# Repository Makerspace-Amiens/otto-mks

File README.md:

# Otto-MKS
Open Source Robot based on Otto, the Walking Robot

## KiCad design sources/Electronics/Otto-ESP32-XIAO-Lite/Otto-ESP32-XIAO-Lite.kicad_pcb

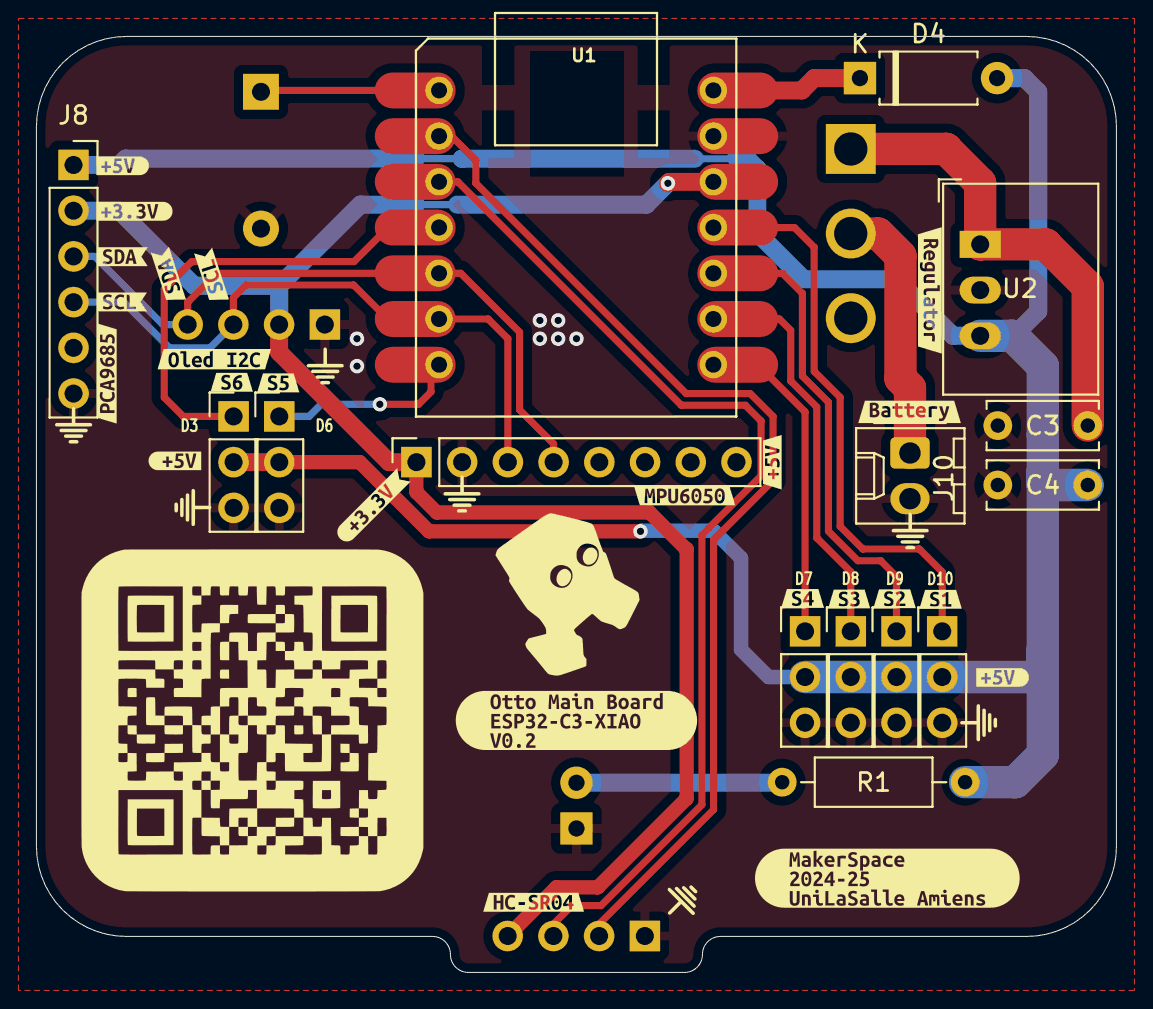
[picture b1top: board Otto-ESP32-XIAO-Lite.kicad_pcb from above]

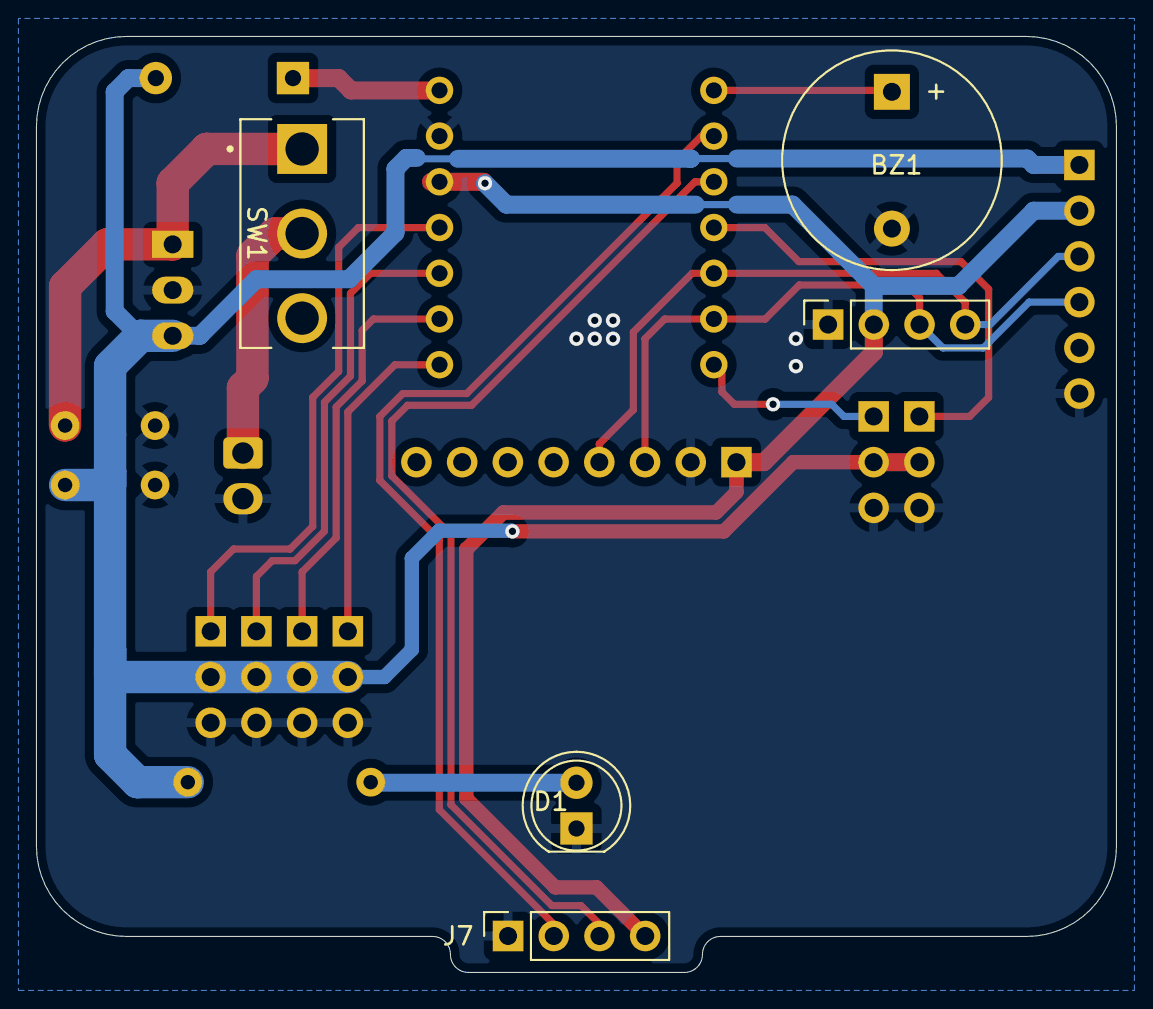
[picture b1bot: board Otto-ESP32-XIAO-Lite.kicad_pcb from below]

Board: 2 copper layers, 60.0 x 52.0 mm, 44 parts (5 on the bottom side), 18 nets.

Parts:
BZ1: Buzzer; Buzzer_12x9.5RM7.6
C3, C4: C_Small; C_Disc_D6.0mm_W2.5mm_P5.00mm
D1: LED_Small; LED_D5.0mm
D4: D_Schottky; D_A-405_P7.62mm_Horizontal
J1, J2, J3, J4, J5, J6: Conn_01x03; PinHeader_1x03_P2.54mm_Vertical
J7: Ultrasonic sensor; PinSocket_1x04_P2.54mm_Vertical
J8: PCA9685; PinSocket_1x06_P2.54mm_Vertical
J10: Conn_01x02; Molex_KK-254_AE-6410-02A_1x02_P2.54mm_Vertical
J12: OLED 0,91" - I2C (SKU21796); PinSocket_1x04_P2.54mm_Vertical
J13: MPU6050; PinSocket_1x08_P2.54mm_Vertical
R1: R_Small; R_Axial_DIN0207_L6.3mm_D2.5mm_P10.16mm_Horizontal
SW1: SW_SPDT; SW_100SP1T1B4M2QE
U1: MOUDLE-SEEEDUINO-XIAO-ESP32C3; MOUDLE14P-SMD-2.54-21X17.8MM
U2: R-78E5.0-1.0; Converter_DCDC_RECOM_R-78E-0.5_THT
kibuzzard-66E45AAF: G***; kibuzzard-66E45AAF
kibuzzard-66E45B4D: G***; kibuzzard-66E45B4D
kibuzzard-66E45B8A: G***; kibuzzard-66E45B8A
kibuzzard-66E45B15: G***; kibuzzard-66E45B15
kibuzzard-66E45B47: G***; kibuzzard-66E45B47
kibuzzard-66E45B51: G***; kibuzzard-66E45B51
kibuzzard-66E45B85: G***; kibuzzard-66E45B85
kibuzzard-66E45BAB, kibuzzard-66E45BAB#2: G***; kibuzzard-66E45BAB
kibuzzard-66E45BBF: G***; kibuzzard-66E45BBF
kibuzzard-66E45BE1: G***; kibuzzard-66E45BE1
kibuzzard-66E45BF0: G***; kibuzzard-66E45BF0
kibuzzard-66E460A4: G***; kibuzzard-66E460A4
kibuzzard-66E460BA: G***; kibuzzard-66E460BA
kibuzzard-66E460D9: G***; kibuzzard-66E460D9
kibuzzard-66E46157: G***; kibuzzard-66E46157
kibuzzard-6707C6B3: G***; kibuzzard-6707C6B3
kibuzzard-6707CFA2: G***; kibuzzard-6707CFA2
kibuzzard-69711E0F: G***; kibuzzard-69711E0F
kibuzzard-676543B8: G***; kibuzzard-676543B8
kibuzzard-6765451E: G***; kibuzzard-6765451E
kibuzzard-6765454D: G***; kibuzzard-6765454D
kibuzzard-67654523: G***; kibuzzard-67654523
kibuzzard-67654588: G***; kibuzzard-67654588

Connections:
+3.3V: J7.4, J8.2, J12.2, J13.1, U1.12 (3V3)
+5V: C4.1, D4.2 (A), J1.2, J2.2, J3.2, J4.2, J5.2, J6.2, J8.1, R1.1, U2.3 (OUT)
+BATT: C3.1, SW1.1 (A), U2.1 (IN)
Buzzer: BZ1.1 (+), U1.1 (PA02_A0_D0)
Echo: J7.2, U1.2 (PA4_A1_D1)
GND: BZ1.2 (-), C3.2, C4.2, D1.1 (K), J1.3, J2.3, J3.3, J4.3, J5.3, J6.3, J7.1, J8.6, J10.2, J12.1, J13.2, U1.13 (GND), U2.2 (GND)
unnamed: D1.2 (A), R1.2
unnamed: D4.1 (K), U1.14 (5V)
unnamed: J10.1, SW1.2 (B)
SCL: J8.4, J12.3, J13.3, U1.6 (PA9_A5_D5_SCL)
SDA: J8.3, J12.4, J13.4, U1.5 (PA8_A4_D4_SDA)
Servo-1: J1.1, U1.11 (PA6_A10_D10_MOSI)
Servo-2: J2.1, U1.10 (PA5_A9_D9_MISO)
Servo-3: J3.1, U1.9 (PA7_A8_D8_SCK)
Servo-4: J4.1, U1.8 (PB09_A7_D7_RX)
Servo-5: J5.1, U1.7 (PB08_A6_D6_TX)
Servo-6: J6.1, U1.4 (PA11_A3_D3)
Trig: J7.3, U1.3 (PA10_A2_D2)

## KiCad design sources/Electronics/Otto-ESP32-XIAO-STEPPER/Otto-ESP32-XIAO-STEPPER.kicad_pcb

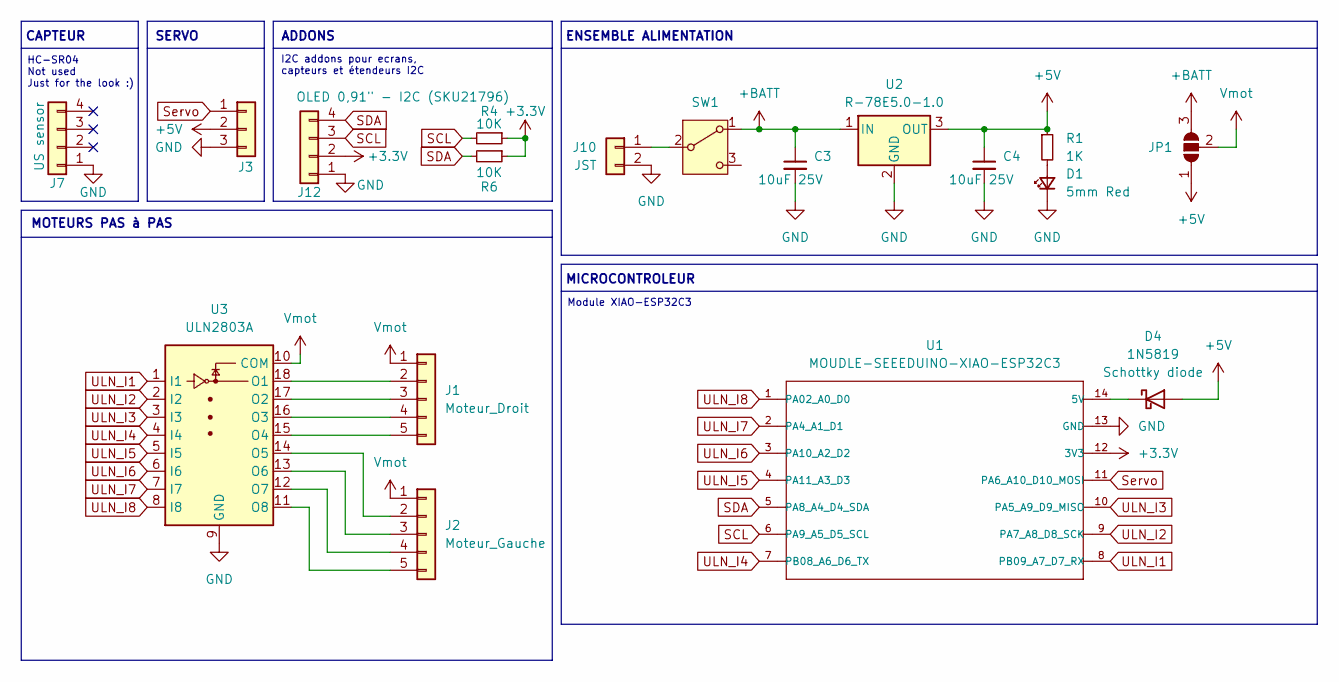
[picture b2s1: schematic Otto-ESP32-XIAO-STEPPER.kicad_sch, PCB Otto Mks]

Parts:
C3, C4: 10uF 25V; C_Disc_D6.0mm_W2.5mm_P5.00mm
D1: 5mm Red; LED_D5.0mm
D4: 1N5819; D_A-405_P7.62mm_Horizontal
J1: Moteur_Droit; JST_XH_B5B-XH-A_1x05_P2.50mm_Vertical
J2: Moteur_Gauche; JST_XH_B5B-XH-A_1x05_P2.50mm_Vertical
J3: Servo; PinHeader_1x03_P2.54mm_Vertical
J7: US sensor; PinSocket_1x04_P2.54mm_Vertical
J10: JST; Molex_KK-254_AE-6410-02A_1x02_P2.54mm_Vertical
J12: OLED 0,91" - I2C (SKU21796); PinSocket_1x04_P2.54mm_Vertical
JP1: SolderJumper_3_Open; SolderJumper-3_P2.0mm_Open_TrianglePad1.0x1.5mm
R1: 1K; R_Axial_DIN0207_L6.3mm_D2.5mm_P10.16mm_Horizontal
R4, R6: 10K; R_1206_3216Metric_Pad1.30x1.75mm_HandSolder
SW1: SW_SPDT; SW_100SP1T1B4M2QE
U1: MOUDLE-SEEEDUINO-XIAO-ESP32C3; XIAO-ESP32C3-DIP
U2: R-78E5.0-1.0; Converter_DCDC_RECOM_R-78E-0.5_THT
U3: ULN2803A; DIP-18_W7.62mm_Socket_LongPads

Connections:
+3.3V: J12.2, R4.1, R6.1, U1.12 (3V3)
+5V: C4.1, D4.2 (A), J3.2, JP1.1 (A), R1.1, U2.3 (OUT)
+BATT: C3.1, JP1.3 (B), SW1.1 (A), U2.1 (IN)
GND: C3.2, C4.2, D1.1 (K), J3.3, J7.1, J10.2, J12.1, U1.13 (GND), U2.2 (GND), U3.9 (GND)
unnamed: D1.2 (A), R1.2
unnamed: D4.1 (K), U1.14 (5V)
unnamed: J1.2, U3.18 (O1)
unnamed: J1.3, U3.17 (O2)
unnamed: J1.4, U3.16 (O3)
unnamed: J1.5, U3.15 (O4)
unnamed: J2.2, U3.14 (O5)
unnamed: J2.3, U3.13 (O6)
unnamed: J2.4, U3.12 (O7)
unnamed: J2.5, U3.11 (O8)
unnamed: J10.1, SW1.2 (B)
SCL: J12.3, R4.2, U1.6 (PA9_A5_D5_SCL)
SDA: J12.4, R6.2, U1.5 (PA8_A4_D4_SDA)
Servo: J3.1, U1.11 (PA6_A10_D10_MOSI)
ULN_I1: U1.8 (PB09_A7_D7_RX), U3.1 (I1)
ULN_I2: U1.9 (PA7_A8_D8_SCK), U3.2 (I2)
ULN_I3: U1.10 (PA5_A9_D9_MISO), U3.3 (I3)
ULN_I4: U1.7 (PB08_A6_D6_TX), U3.4 (I4)
ULN_I5: U1.4 (PA11_A3_D3), U3.5 (I5)
ULN_I6: U1.3 (PA10_A2_D2), U3.6 (I6)
ULN_I7: U1.2 (PA4_A1_D1), U3.7 (I7)
ULN_I8: U1.1 (PA02_A0_D0), U3.8 (I8)
Vmot: J1.1, J2.1, JP1.2 (C), U3.10 (COM)

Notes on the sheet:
HC-SR04 Not used Just for the look :)
CAPTEUR
MOTEURS PAS à PAS
ADDONS
ENSEMBLE ALIMENTATION
SERVO
Module XIAO-ESP32C3
I2C addons pour ecrans, capteurs et étendeurs I2C
MICROCONTROLEUR

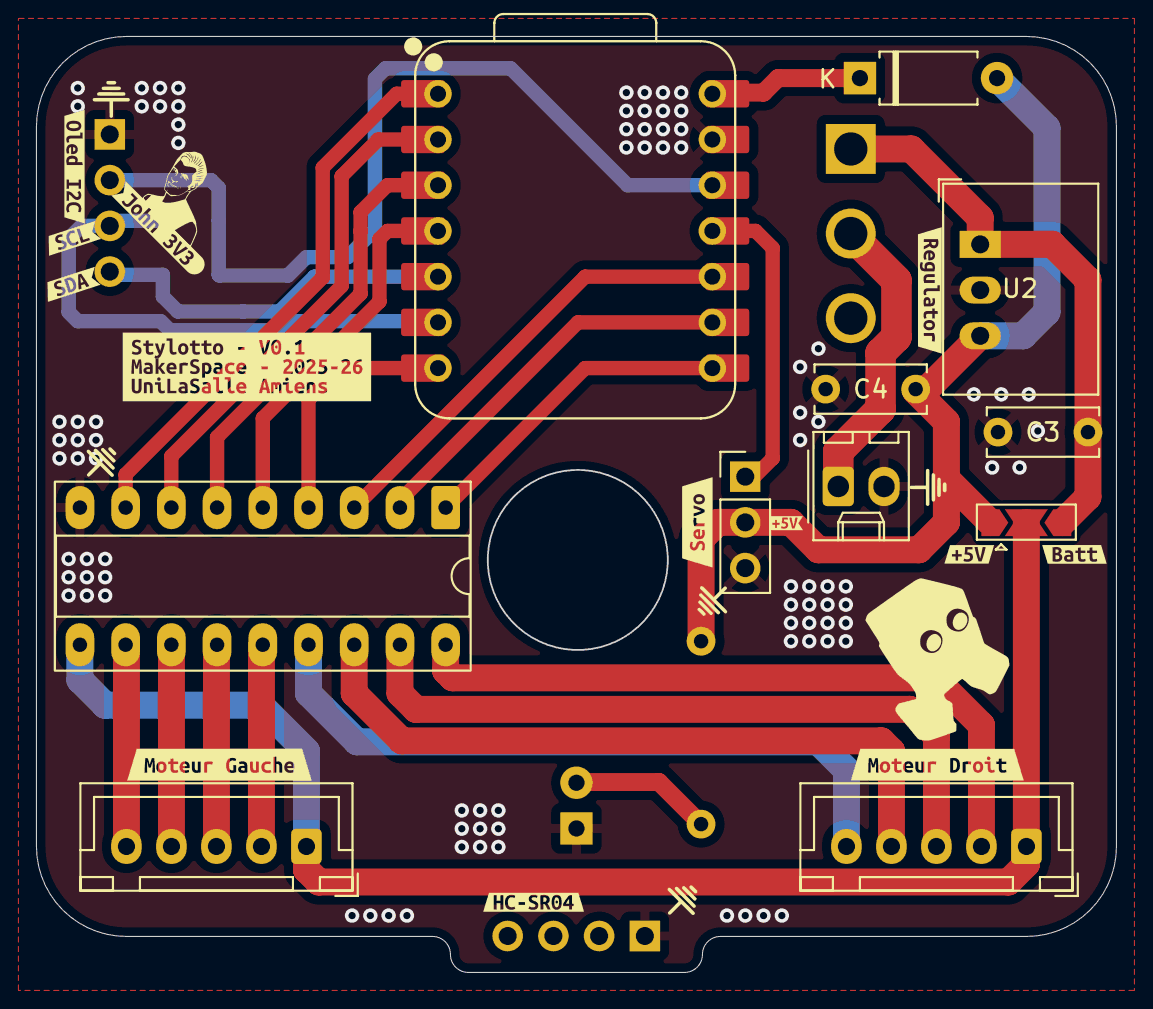
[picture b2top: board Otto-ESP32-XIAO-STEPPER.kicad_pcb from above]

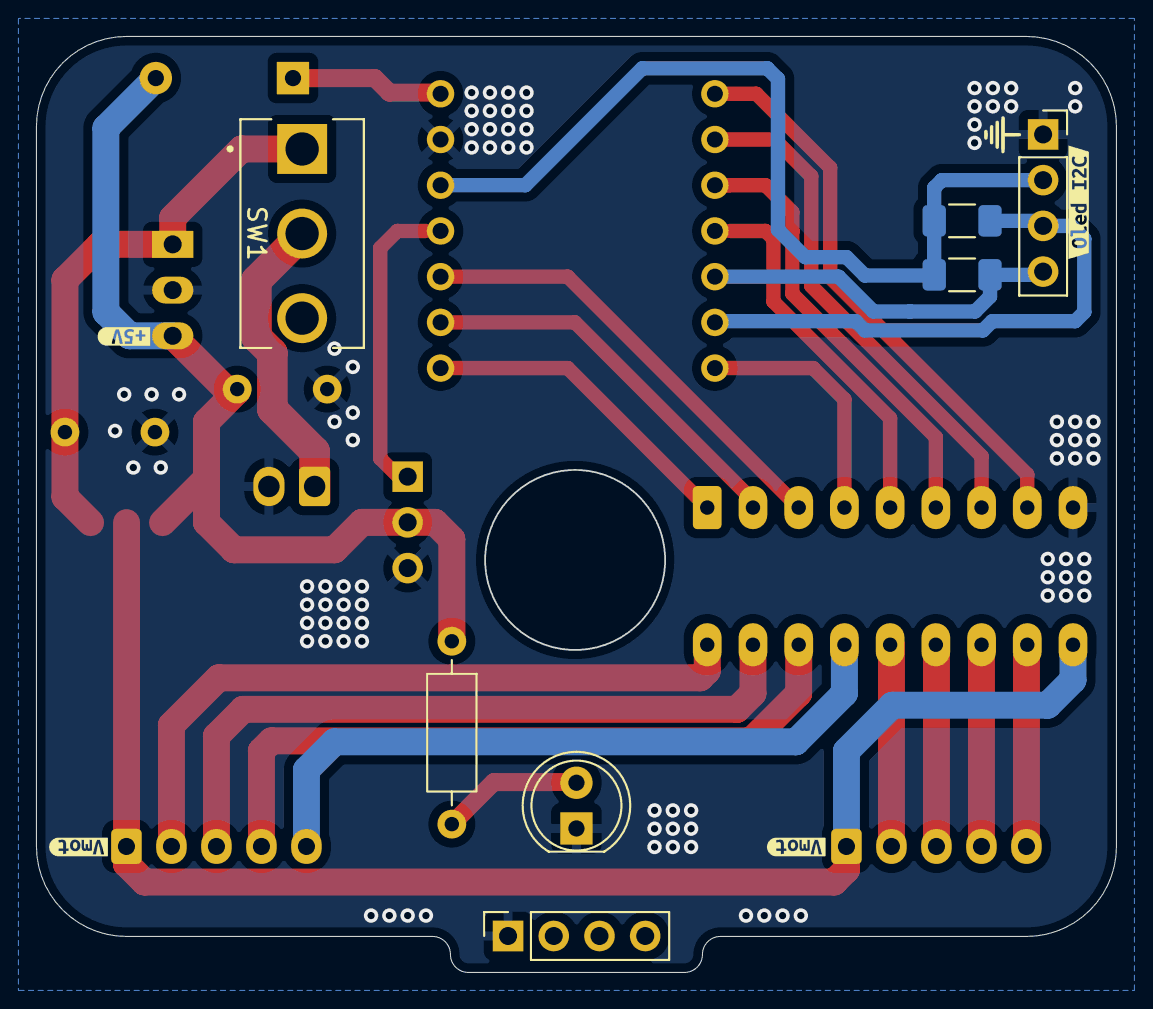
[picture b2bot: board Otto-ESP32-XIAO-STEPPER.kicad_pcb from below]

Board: 2 copper layers, 60.0 x 52.0 mm, 35 parts (11 on the bottom side), 27 nets.

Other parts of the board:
kibuzzard-66E45BAB: G***; kibuzzard-66E45BAB
kibuzzard-66E46157: G***; kibuzzard-66E46157
kibuzzard-67E17B13: G***; kibuzzard-67E17B13
kibuzzard-67E17CB8, kibuzzard-67E17CB8#2: G***; kibuzzard-67E17CB8
kibuzzard-68A443B3: G***; kibuzzard-68A443B3
kibuzzard-68A443C3: G***; kibuzzard-68A443C3
kibuzzard-68A443E1, kibuzzard-68A443E1#2: G***; kibuzzard-68A443E1
kibuzzard-68A4434B: G***; kibuzzard-68A4434B
kibuzzard-68A4489E: G***; kibuzzard-68A4489E
kibuzzard-68A44298: G***; kibuzzard-68A44298
kibuzzard-68A44346: G***; kibuzzard-68A44346
kibuzzard-68A44445: G***; kibuzzard-68A44445
kibuzzard-6707C6B3: G***; kibuzzard-6707C6B3
kibuzzard-6765451E: G***; kibuzzard-6765451E
kibuzzard-67654523: G***; kibuzzard-67654523

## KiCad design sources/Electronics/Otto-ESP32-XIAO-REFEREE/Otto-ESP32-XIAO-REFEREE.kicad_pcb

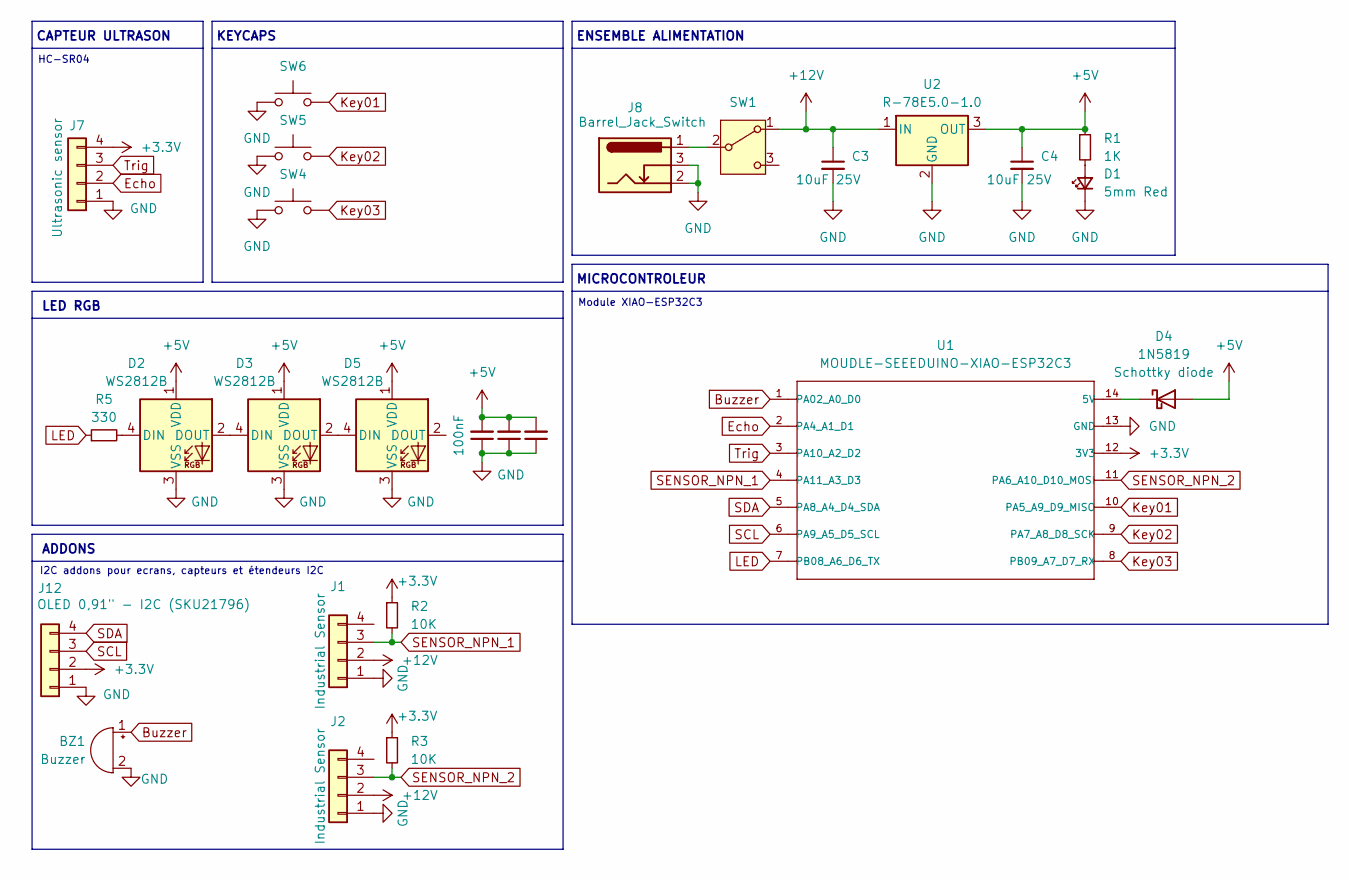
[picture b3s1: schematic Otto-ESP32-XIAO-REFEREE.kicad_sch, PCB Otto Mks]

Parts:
BZ1: Buzzer; Buzzer_12x9.5RM7.6
C3, C4: 10uF 25V; C_Disc_D6.0mm_W2.5mm_P5.00mm
C5, C6, C7: 100nF; C_1206_3216Metric_Pad1.33x1.80mm_HandSolder
D1: 5mm Red; LED_1206_3216Metric_Pad1.42x1.75mm_HandSolder
D2, D3, D5: WS2812B; LED_WS2812B_PLCC4_5.0x5.0mm_P3.2mm
D4: 1N5819; D_A-405_P7.62mm_Horizontal
J1, J2: Industrial Sensor; Molex_KK-254_AE-6410-04A_1x04_P2.54mm_Vertical
J7: Ultrasonic sensor; PinSocket_1x04_P2.54mm_Vertical
J8: Barrel_Jack_Switch; BarrelJack_Horizontal
J12: OLED 0,91" - I2C (SKU21796); PinSocket_1x04_P2.54mm_Vertical
R1: 1K; R_1206_3216Metric_Pad1.30x1.75mm_HandSolder
R2, R3: 10K; R_1206_3216Metric_Pad1.30x1.75mm_HandSolder
R5: 330; R_1206_3216Metric_Pad1.30x1.75mm_HandSolder
SW1: SW_SPDT; SW_100SP1T1B4M2QE
SW4, SW5, SW6: CherryMX; SW_Cherry_MX_1.00u_PCB
U1: MOUDLE-SEEEDUINO-XIAO-ESP32C3; XIAO-ESP32C3-DIP
U2: R-78E5.0-1.0; Converter_DCDC_RECOM_R-78E-0.5_THT

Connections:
+3.3V: J7.4, J12.2, R2.1, R3.1, U1.12 (3V3); also elsewhere on the board
+5V: C4.1, C5.2, C6.2, C7.2, D2.1 (VDD), D3.1 (VDD), D4.2 (A), D5.1 (VDD), R1.1, U2.3 (OUT)
+12V: C3.1, J1.2, J2.2, SW1.1 (A), U2.1 (IN)
Buzzer: BZ1.1 (+), U1.1 (PA02_A0_D0)
Echo: J7.2, U1.2 (PA4_A1_D1)
GND: BZ1.2 (-), C3.2, C4.2, C5.1, C6.1, C7.1, D1.1 (K), D2.3 (VSS), D3.3 (VSS), D5.3 (VSS), J1.1, J2.1, J7.1, J8.2, J8.3, J12.1, SW4.1, SW5.1, SW6.1, U1.13 (GND), U2.2 (GND)
Key01: SW6.2, U1.10 (PA5_A9_D9_MISO)
Key02: SW5.2, U1.9 (PA7_A8_D8_SCK)
Key03: SW4.2, U1.8 (PB09_A7_D7_RX)
LED: R5.1, U1.7 (PB08_A6_D6_TX)
unnamed: D1.2 (A), R1.2
unnamed: D2.4 (DIN), R5.2
unnamed: D2.2 (DOUT), D3.4 (DIN)
unnamed: D3.2 (DOUT), D5.4 (DIN)
unnamed: D4.1 (K), U1.14 (5V)
unnamed: J8.1, SW1.2 (B)
SCL: J12.3, U1.6 (PA9_A5_D5_SCL); also elsewhere on the board
SDA: J12.4, U1.5 (PA8_A4_D4_SDA); also elsewhere on the board
SENSOR_NPN_1: J1.3, R2.2, U1.4 (PA11_A3_D3)
SENSOR_NPN_2: J2.3, R3.2, U1.11 (PA6_A10_D10_MOSI)
Trig: J7.3, U1.3 (PA10_A2_D2)

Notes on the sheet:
HC-SR04
CAPTEUR ULTRASON
LED RGB
ADDONS
ENSEMBLE ALIMENTATION
KEYCAPS
Module XIAO-ESP32C3
I2C addons pour ecrans, capteurs et étendeurs I2C
MICROCONTROLEUR

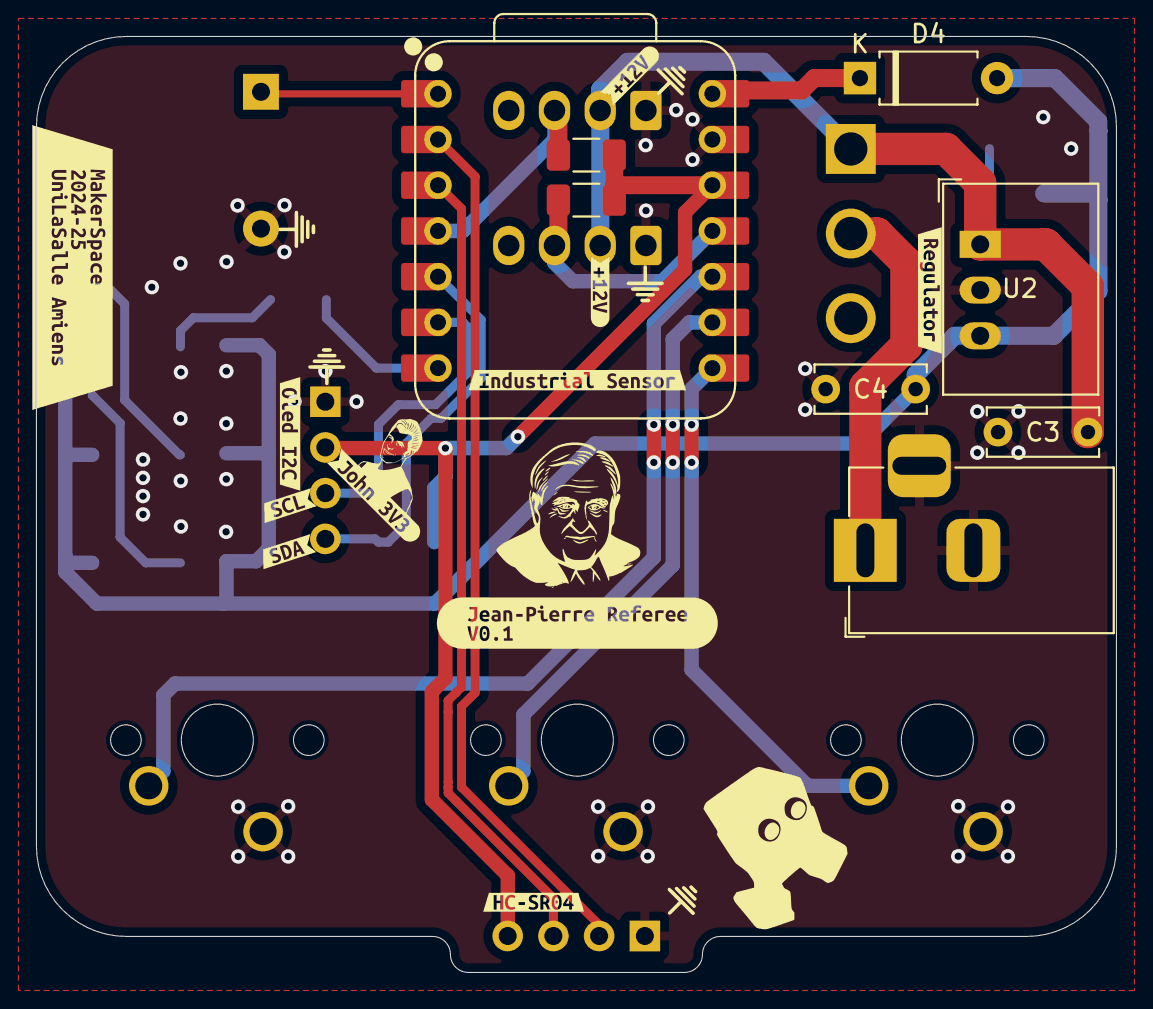
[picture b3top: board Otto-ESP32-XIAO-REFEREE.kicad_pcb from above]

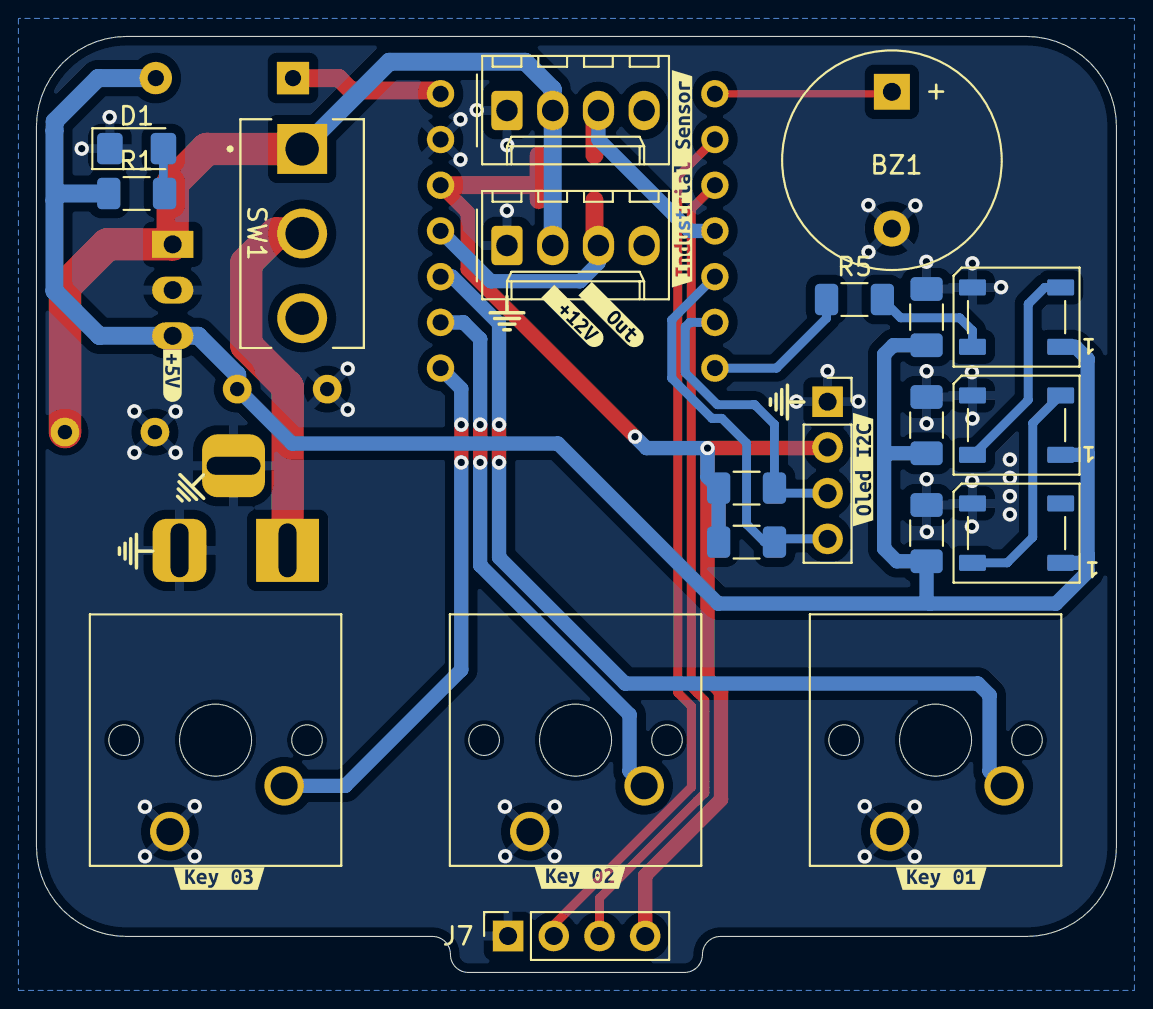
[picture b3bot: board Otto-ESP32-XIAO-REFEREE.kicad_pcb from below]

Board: 2 copper layers, 60.0 x 52.0 mm, 47 parts (28 on the bottom side), 21 nets.

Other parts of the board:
R4, R6: 10K; R_1206_3216Metric_Pad1.30x1.75mm_HandSolder
kibuzzard-66E45BAB: G***; kibuzzard-66E45BAB
kibuzzard-66E46157: G***; kibuzzard-66E46157
kibuzzard-67E17B13: G***; kibuzzard-67E17B13
kibuzzard-67E17C5A, kibuzzard-67E17C5A#2: G***; kibuzzard-67E17C5A
kibuzzard-67E17C70: G***; kibuzzard-67E17C70
kibuzzard-67E17CA6: G***; kibuzzard-67E17CA6
kibuzzard-67E17CB8, kibuzzard-67E17CB8#2: G***; kibuzzard-67E17CB8
kibuzzard-67E17911: G***; kibuzzard-67E17911
kibuzzard-67E17954: G***; kibuzzard-67E17954
kibuzzard-67EAB5AA: G***; kibuzzard-67EAB5AA
kibuzzard-67EAB5C2: G***; kibuzzard-67EAB5C2
kibuzzard-67EAB5C7: G***; kibuzzard-67EAB5C7
kibuzzard-67EAB37B: G***; kibuzzard-67EAB37B
kibuzzard-67EAB421: G***; kibuzzard-67EAB421
kibuzzard-6707C6B3: G***; kibuzzard-6707C6B3
kibuzzard-6765451E: G***; kibuzzard-6765451E
kibuzzard-67654523: G***; kibuzzard-67654523

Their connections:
+3.3V: R4.1, R6.1; also elsewhere on the board
SCL: R4.2; also elsewhere on the board
SDA: R6.2; also elsewhere on the board

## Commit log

2024-09-11 Step Stick version
2024-09-11 export 3D models
2024-09-11 update infos on 3D models
2024-09-12 add TMC, oled and 3D models
2024-09-12 quick update
2024-09-12 Change US sensor orientation. Add MPU6090
2024-09-12 update save
2024-09-13 routing and documentation
2024-09-13 correct short circuit between gnd and 3.3V
2024-09-24 enlarge pins on C3 socket
2024-10-10 New PCB lite version
2024-10-10 add documentation site
2024-10-10 Update bulma-clean-theme requirement from 1.0.3 to 1.1.0
    Updates the requirements on [bulma-clean-theme](https://github.com/chrisrhymes/bulma-clean-theme) to permit the latest version.
    - [Release notes](https://github.com/chrisrhymes/bulma-clean-theme/releases)
    - [Changelog](https://github.com/chrisrhymes/bulma-clean-theme/blob/master/changelog.txt)
    - [Commits](https://github.com/chrisrhymes/bulma-clean-theme/compare/v1.0.3...v1.1.0)
    ---
    updated-dependencies:
2024-10-10 add qrCode - clean PCB
2024-10-10 New Step
2024-10-10 first update doc - Ready to be completed
2024-10-10 fix typo
2024-10-10 Clean up the Schematic
2024-10-10 New tree structure
2024-10-10 change links
2024-10-21 New Expansion Board Version
2024-10-23 Fix Burger Color
2024-10-24 add authors
2024-12-09 fix add 3d model viewer
2024-12-11 update with craft-the-docs
2024-12-13 Created and updated onshape-project tutorial
2024-12-20 New version
    - Add pinout servo documentation
    - Remove diode D2
2025-01-06 Fixed everything yay - added new tutorials and docs
2025-01-15 added basic code REMOTE XY
2025-01-20 Update bulma-clean-theme requirement from 1.1.0 to 1.2.0
    Updates the requirements on [bulma-clean-theme](https://github.com/chrisrhymes/bulma-clean-theme) to permit the latest version.
    - [Release notes](https://github.com/chrisrhymes/bulma-clean-theme/releases)
    - [Changelog](https://github.com/chrisrhymes/bulma-clean-theme/blob/master/changelog.txt)
    - [Commits](https://github.com/chrisrhymes/bulma-clean-theme/compare/v1.1.0...v1.2.0)
    ---
    updated-dependencies:
2025-01-21 update documentation
2025-01-21 new content
2025-01-21 change url
2025-01-27 add ressources
2025-01-27 discover arduino - first commit
2025-01-27 new tuto discover arduino
2025-01-27 fix image
2025-01-27 nex content
2025-01-29 Added steps for assembly
2025-01-30 Kept working on assemble tutorial
2025-01-30 modifications on assembly tutorial
2025-01-30 Reordered Tutorials
2025-01-30 Fixed dead link to Servo tutorial
2025-01-30 Added a danger sign and other tweaks
2025-01-31 Removed Hardware tabs
2025-01-31 New épreuves
2025-02-03 Tweaks on information page and epreuves pages
2025-02-04 Cleaned up tutorials
2025-02-04 Added and modified tutorials
2025-02-05 Fixed dead links
2025-02-05 Fixed home page callouts and dead links
2025-02-05 Fixed typo and ottolympiades page
2025-02-10 Added content on ottolympiades homologation
2025-02-11 Added info on homologation rules
2025-02-20 Added and modified épreuves
2025-02-24 Added stuff to épreuves
2025-02-25 modified Tire a la corde épreuve
2025-02-25 New and improved favicon and new illustrations on tir_a_la_corde
2025-02-25 Added Presentation section and cleaned up Epreuves
2025-02-26 Added Attendus académiques
2025-02-27 Added Obstacle course épreuve en modified homologation
2025-03-07 Modified obstacle course
2025-03-10 Modified distance for Race and uploaded new graphics
2025-03-17 Added 3D model to Sumo Epreuve page
2025-03-18 Update 3D model
2025-03-24 Added illustration to obstacle course
2025-03-24 New PCB JP Referee
2025-03-24 update Schematics
2025-03-26 tried adding 3D model to SUMO
2025-03-27 fix sumo_model with dimensions
2025-03-27 hide global loading bar
2025-03-31 add silkscreen
2025-04-01 add I2C resistors
2025-04-04 refactor for 3D export
2025-04-07 switch cap
2025-04-24 Updated rules
2025-04-24 Modified baremes
2025-04-24 Otto referee Firmware
2025-04-30 Modified finale rules for Sumo
2025-05-09 Added 3D models
2025-05-13 Added 3d model obstacle course and fixed titles
2025-05-16 modified winning criterias
2025-05-22 Reversed screen and added Barcode
2025-06-20 Fixed typo
2025-08-19 New Robot Stepper PCB
2025-08-22 backup
2026-01-21 add header pin option for XIAO
2026-01-21 New kicad version
